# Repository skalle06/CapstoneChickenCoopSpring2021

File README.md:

# CapstoneChickenCoopSpring2021

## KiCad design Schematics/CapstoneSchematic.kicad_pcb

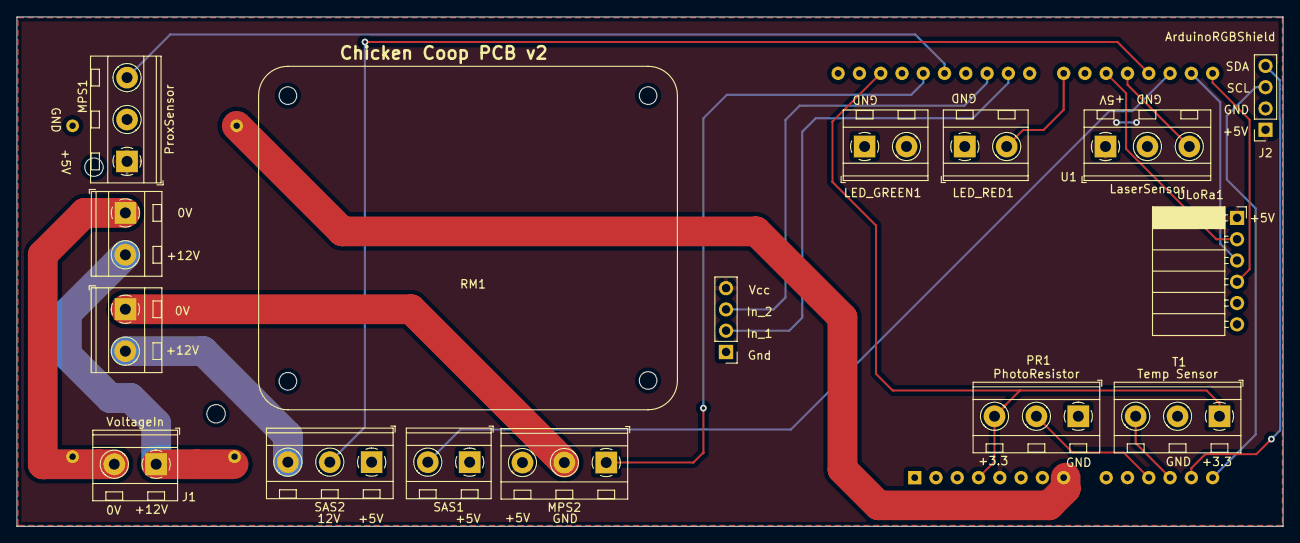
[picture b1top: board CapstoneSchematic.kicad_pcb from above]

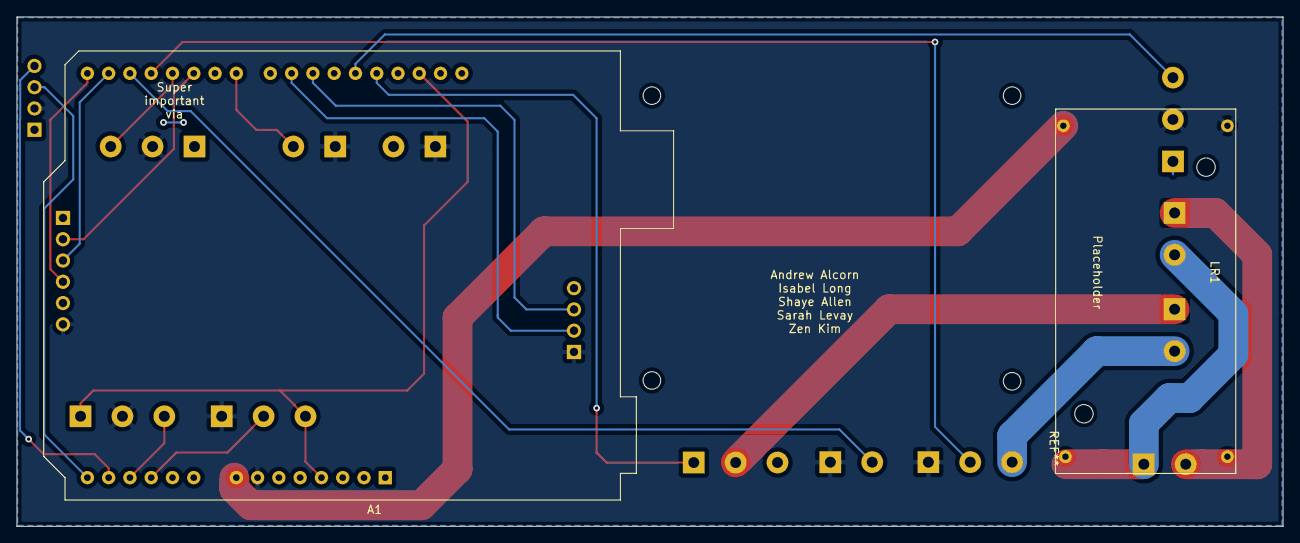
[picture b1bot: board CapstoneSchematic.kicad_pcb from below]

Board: 2 copper layers, 151.1 x 60.8 mm, 15 parts (2 on the bottom side), 21 nets.

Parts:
A1: Arduino_UNO_R3
J1: VoltageIn; TerminalBlock_MetzConnect_Type094_RT03502HBLU_1x02_P5.00mm_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
J2: ArduinoRGBShield; PinSocket_1x04_P2.54mm_Vertical
LED_GREEN1: 200; TerminalBlock_MetzConnect_Type094_RT03502HBLU_1x02_P5.00mm_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
LED_RED1: 200; TerminalBlock_MetzConnect_Type094_RT03502HBLU_1x02_P5.00mm_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
LR1: Linear_Regulator; Linear Regulator
MPS1, MPS2: ProxSensor; TerminalBlock_MetzConnect_Type094_RT03503HBLU_1x03_P5.00mm_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
PR1: PhotoResistor; TerminalBlock_MetzConnect_Type094_RT03503HBLU_1x03_P5.00mm_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
RM1: 2RelayModule; 2 Channels Relay
SAS1: SnapActionSwitch; TerminalBlock_MetzConnect_Type094_RT03502HBLU_1x02_P5.00mm_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
SAS2: SnapActionSwitch; TerminalBlock_MetzConnect_Type094_RT03503HBLU_1x03_P5.00mm_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
T1: Temp Sensor; TerminalBlock_MetzConnect_Type094_RT03503HBLU_1x03_P5.00mm_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
U1: LaserSensor; TerminalBlock_MetzConnect_Type094_RT03503HBLU_1x03_P5.00mm_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
ULoRa1: LoRa; PinSocket_1x06_P2.54mm_Horizontal

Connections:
0: J1.2, LR1.2, RM1.8
+3V3: A1.4, A1.30, PR1.3, T1.4
+5V: A1.5, J2.1, LED_GREEN1.2, MPS1.1, MPS2.1, RM1.4, U1.1, ULoRa1.1
+12V: J1.1, LR1.1, RM1.10
/IN1: A1.24, RM1.2
/IN2: A1.25, RM1.3
/LED_R: A1.22, LED_RED1.2
/LoRa2: A1.20, ULoRa1.2
/SAS_Int1: A1.17, SAS1.4
/SAS_Int2: A1.18, SAS2.2
GND: A1.7, J2.2, LED_GREEN1.1, LED_RED1.1, LR1.4, MPS1.2, PR1.1, RM1.1, SAS1.1, SAS2.1, T1.2, U1.2, ULoRa1.6
unnamed: A1.8, LR1.3
unnamed: A1.11, PR1.2
unnamed: A1.12, T1.3
unnamed: A1.13, J2.4
unnamed: A1.14, J2.3
unnamed: A1.19, U1.3
unnamed: A1.27, MPS1.3
unnamed: A1.28, MPS2.3
unnamed: RM1.9, SAS2.4
unnamed: MPS2.2, RM1.6
